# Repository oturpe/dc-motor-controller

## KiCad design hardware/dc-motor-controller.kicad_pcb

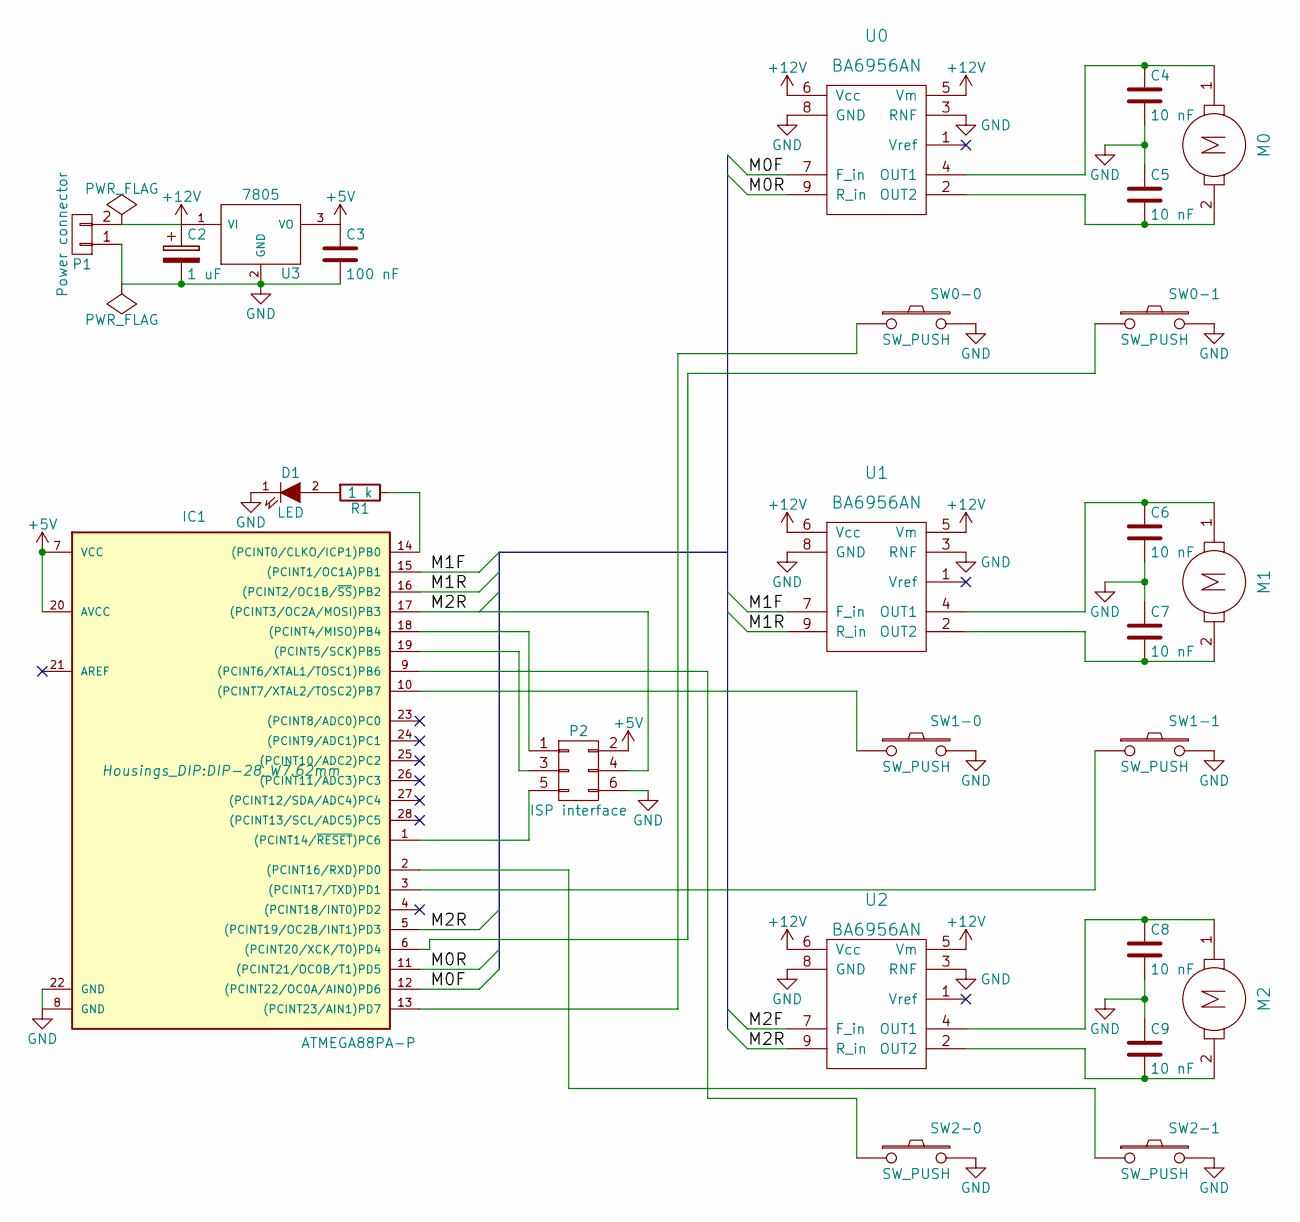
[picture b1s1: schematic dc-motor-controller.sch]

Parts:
C2: 1 uF; C_Radial_D5_L6_P2.5
C3: 100 nF; C_Rect_L7_W2.5_P5
C4, C5, C6, C7, C8, C9: 10 nF; C_Rect_L7_W2.5_P5
D1: LED; LED-3MM
IC1: ATMEGA88PA-P; DIP-28_W7.62mm
M0, M1, M2: DC_motor; Big_green_chocolate_1x2
P1: Power connector; Small_green_chocolade_1x2
P2: ISP interface; Borg_hedged_2x03
R1: 1 k; Resistor_Horizontal_RM10mm
SW0-0, SW0-1, SW1-0, SW1-1, SW2-0, SW2-1: SW_PUSH; Small_green_chocolade_1x2
U0, U1, U2: BA6956AN; SIP9_Housing
U3: 7805; TO-220_Neutral123_Vertical

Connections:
+5V: C3.1, IC1.7 (VCC), IC1.20 (AVCC), P2.2, U3.3 (VO)
+12V: C2.1, P1.2, U0.5 (Vm), U0.6 (Vcc), U1.5 (Vm), U1.6 (Vcc), U2.5 (Vm), U2.6 (Vcc), U3.1 (VI)
/M0F: IC1.12 ((PCINT22/OC0A/AIN0)PD6), U0.7 (F_in)
/M0R: IC1.11 ((PCINT21/OC0B/T1)PD5), U0.9 (R_in)
/M1F: IC1.15 ((PCINT1/OC1A)PB1), U1.7 (F_in)
/M1R: IC1.16 ((PCINT2/OC1B/~SS~)PB2), U1.9 (R_in)
/M2R: IC1.5 ((PCINT19/OC2B/INT1)PD3), IC1.17 ((PCINT3/OC2A/MOSI)PB3), P2.4, U2.9 (R_in)
GND: C2.2, C3.2, C4.2, C5.1, C6.2, C7.1, C8.2, C9.1, D1.1 (K), IC1.8 (GND), IC1.22 (GND), P1.1, P2.6, SW0-0.2, SW0-1.2, SW1-0.2, SW1-1.2, SW2-0.2, SW2-1.2, U0.3 (RNF), U0.8 (GND), U1.3 (RNF), U1.8 (GND), U2.3 (RNF), U2.8 (GND), U3.2 (GND)
unnamed: C4.1, M0.1, U0.4 (OUT1)
unnamed: C5.2, M0.2, U0.2 (OUT2)
unnamed: C6.1, M1.1, U1.4 (OUT1)
unnamed: C7.2, M1.2, U1.2 (OUT2)
unnamed: C8.1, M2.1, U2.4 (OUT1)
unnamed: C9.2, M2.2, U2.2 (OUT2)
unnamed: D1.2 (A), R1.2
unnamed: IC1.1 ((PCINT14/~RESET~)PC6), P2.5
unnamed: IC1.2 ((PCINT16/RXD)PD0), SW2-1.1
unnamed: IC1.3 ((PCINT17/TXD)PD1), SW1-1.1
unnamed: IC1.6 ((PCINT20/XCK/T0)PD4), SW0-1.1
unnamed: IC1.9 ((PCINT6/XTAL1/TOSC1)PB6), SW2-0.1
unnamed: IC1.10 ((PCINT7/XTAL2/TOSC2)PB7), SW1-0.1
unnamed: IC1.13 ((PCINT23/AIN1)PD7), SW0-0.1
unnamed: IC1.14 ((PCINT0/CLKO/ICP1)PB0), R1.1
unnamed: IC1.18 ((PCINT4/MISO)PB4), P2.1
unnamed: IC1.19 ((PCINT5/SCK)PB5), P2.3

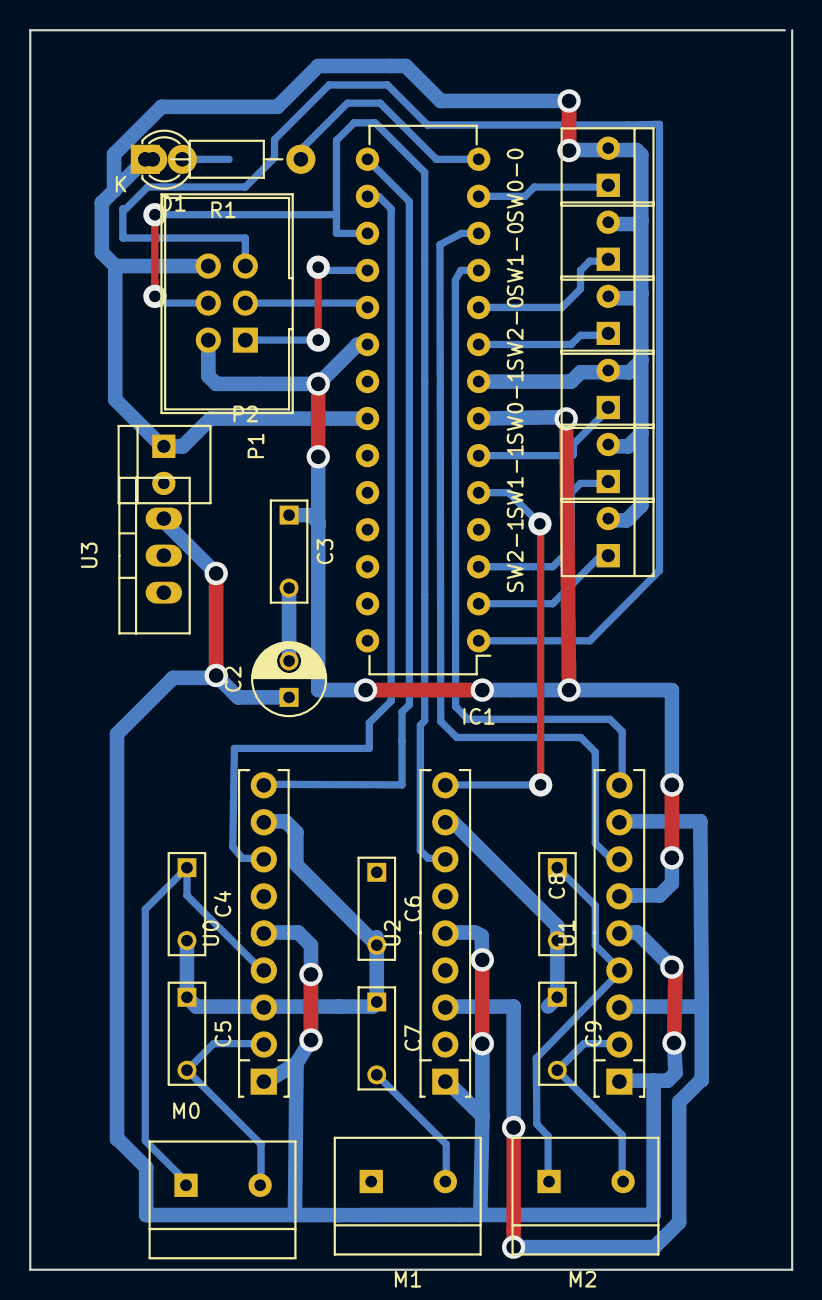
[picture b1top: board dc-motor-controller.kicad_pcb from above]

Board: 2 copper layers, 52.2 x 85.0 mm, 26 parts (0 on the bottom side), 25 nets.

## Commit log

2016-05-30 Initial commit, contains schematic and a single-sided pcb layout
2016-05-30 Some change (?)
2016-06-18 Fix problem in ignoring output production files
2016-06-18 Some changes after reviewing the printed circuit board
2016-06-18 Add generic sample program that utilizes all switches and motors
2016-06-19 Disable fuse writing as there is certainty if the values are correct
2016-06-19 Rename Atmega88pUtils to more general Atmega8Utils
2016-06-19 Updated gitignore file, remove some accidentally stored KiCad backup files
2016-06-19 Improved part numbering of schematic
2016-06-19 Completed sample code
2016-06-20 Typo fix
2016-06-21 Improved indicator sequence, removing glitch at counter overflow
2016-06-22 Fix indicator code bug
2016-06-22 Add a power switch to schemaic
2016-06-22 Update schematic annotation
2016-06-22 Fix a bug affecting the initial speed of motors 2 and 3
2016-06-22 Add trimmers for analog voltage control to schematic
